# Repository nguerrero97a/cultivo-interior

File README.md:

# cultivo-interior

Dispositivo de control y monitoreo de un cultivo en un modulo de interior.

Diseñado por Nicolás Guerrero Arévalo.

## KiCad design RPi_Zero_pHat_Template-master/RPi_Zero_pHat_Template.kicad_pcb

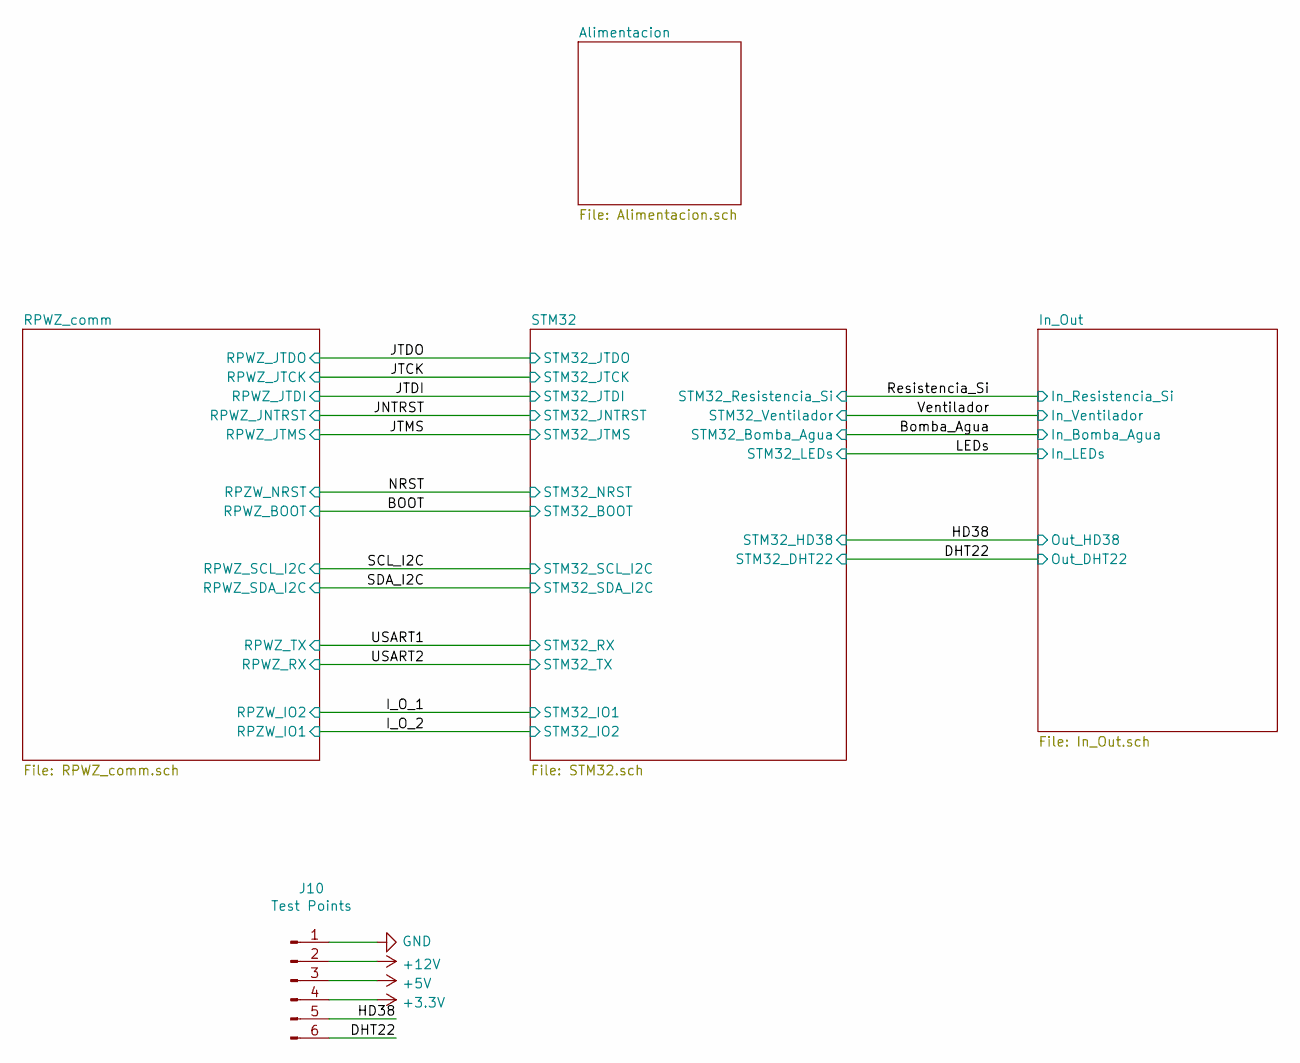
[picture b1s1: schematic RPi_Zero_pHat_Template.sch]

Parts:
J10: Test Points; PinHeader_1x06_P2.54mm_Vertical

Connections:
+3V3: J10.4; also elsewhere on the board
+5V: J10.3; also elsewhere on the board
+12V: J10.2; also elsewhere on the board
/DHT22: J10.6; also elsewhere on the board
/HD38: J10.5; also elsewhere on the board
GND: J10.1; also elsewhere on the board

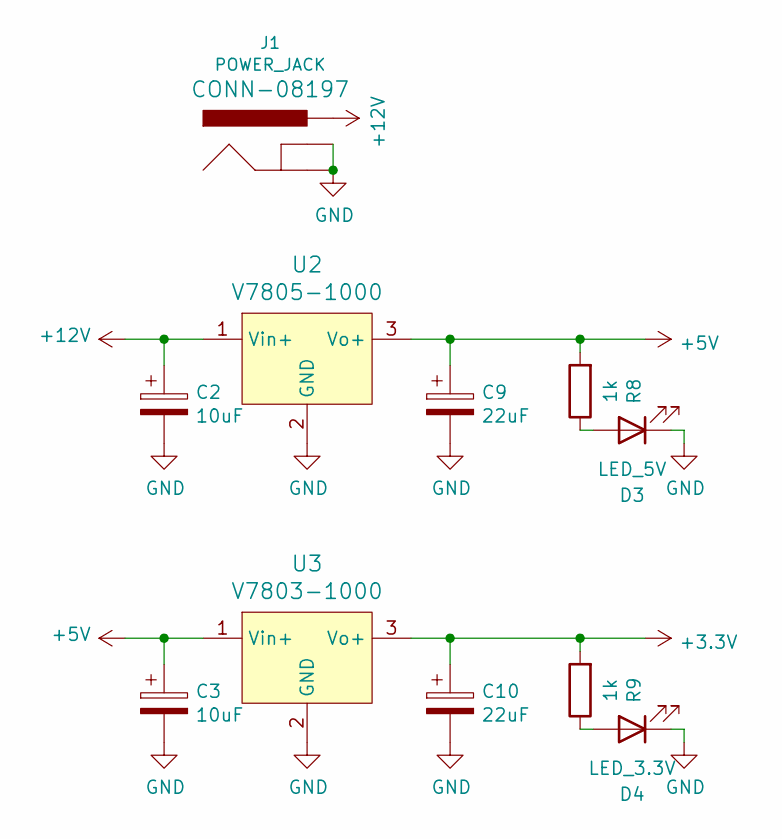
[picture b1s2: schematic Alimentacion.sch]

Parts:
C2, C3: 10uF; CP_Elec_4x5.8
C9, C10: 22uF; CP_Elec_3x5.4
D3: LED_5V; LED_0805_2012Metric
D4: LED_3.3V; LED_0805_2012Metric
J1: POWER_JACK; POWER_JACK_PTH
R8, R9: 1k; R_0805_2012Metric
U2: V7805-1000; 3-SIP_Module_V7805-1000; MPN V7805-1000; Digi-Key_PN 102-1715-ND
U3: V7803-1000; 3-SIP_Module_V7805-1000; MPN V7805-1000; Digi-Key_PN 102-1715-ND

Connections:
+3V3: C10.1, R9.2, U3.3 (Vo+); also elsewhere on the board
+5V: C3.1, C9.1, R8.2, U2.3 (Vo+), U3.1 (Vin+); also elsewhere on the board
+12V: C2.1, J1.PWR, U2.1 (Vin+); also elsewhere on the board
GND: C2.2, C3.2, C9.2, C10.2, D3.1 (K), D4.1 (K), J1.GND, J1.GNDB (GNDBREAK), U2.2 (GND), U3.2 (GND); also elsewhere on the board
unnamed: D3.2 (A), R8.1
unnamed: D4.2 (A), R9.1

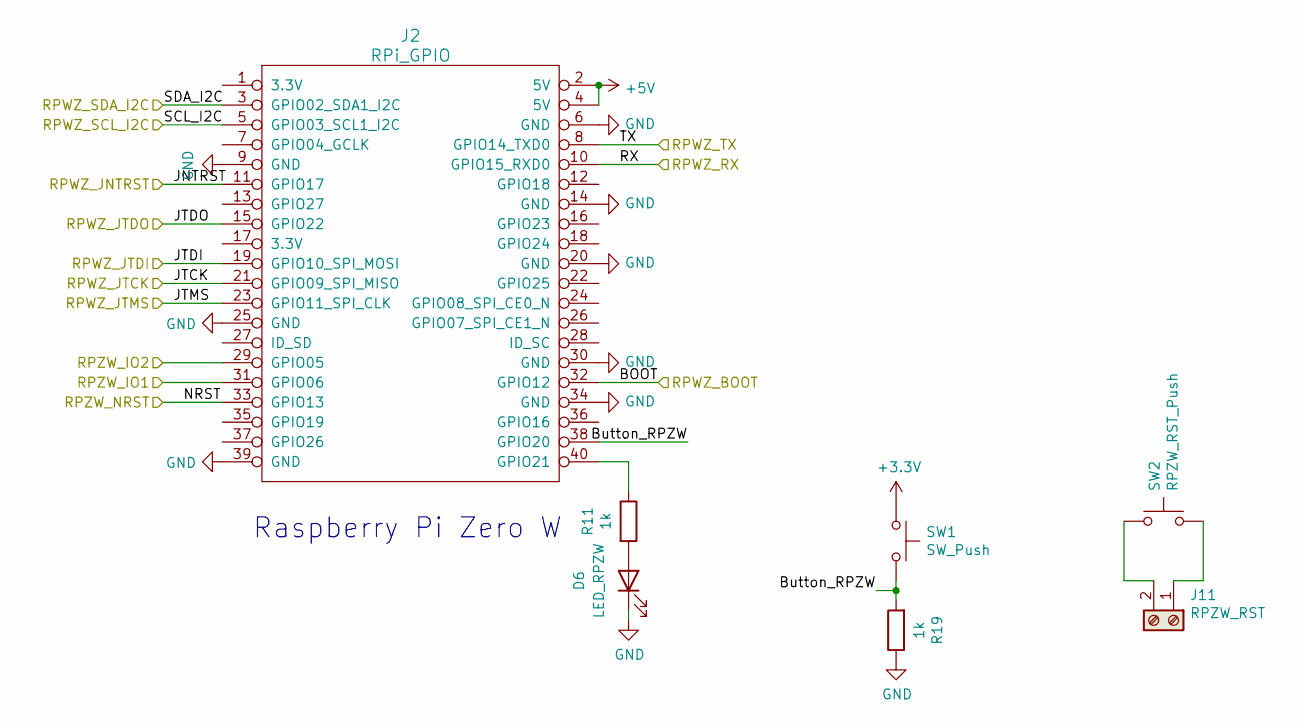
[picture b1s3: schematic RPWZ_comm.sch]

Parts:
D6: LED_RPZW; LED_0805_2012Metric
J2: RPi_GPIO; PinHeader_2x20_P2.54mm_Vertical
J11: RPZW_RST; PinHeader_1x02_P2.54mm_Vertical
R11, R19: 1k; R_0805_2012Metric
SW1: SW_Push; SW_PUSH_6mm_H4.3mm
SW2: RPZW_RST_Push; SW_PUSH_6mm_H4.3mm

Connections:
+3V3: SW1.1; also elsewhere on the board
+5V: J2.2 (5V), J2.4 (5V); also elsewhere on the board
/BOOT: J2.32 (GPIO12); also elsewhere on the board
/I_O_1: J2.29 (GPIO05); also elsewhere on the board
/I_O_2: J2.31 (GPIO06); also elsewhere on the board
/JNTRST: J2.11 (GPIO17); also elsewhere on the board
/JTCK: J2.21 (GPIO09_SPI_MISO); also elsewhere on the board
/JTDI: J2.19 (GPIO10_SPI_MOSI); also elsewhere on the board
/JTDO: J2.15 (GPIO22); also elsewhere on the board
/JTMS: J2.23 (GPIO11_SPI_CLK); also elsewhere on the board
/NRST: J2.33 (GPIO13); also elsewhere on the board
/RPWZ_comm/Button_RPZW: J2.38 (GPIO20), R19.2, SW1.2
/SCL_I2C: J2.5 (GPIO03_SCL1_I2C); also elsewhere on the board
/SDA_I2C: J2.3 (GPIO02_SDA1_I2C); also elsewhere on the board
/USART1: J2.8 (GPIO14_TXD0); also elsewhere on the board
/USART2: J2.10 (GPIO15_RXD0); also elsewhere on the board
GND: D6.1 (K), J2.6 (GND), J2.9 (GND), J2.14 (GND), J2.20 (GND), J2.25 (GND), J2.30 (GND), J2.34 (GND), J2.39 (GND), R19.1; also elsewhere on the board
unnamed: D6.2 (A), R11.2
unnamed: J2.40 (GPIO21), R11.1
unnamed: J11.1, SW2.2
unnamed: J11.2, SW2.1

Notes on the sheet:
Raspberry Pi Zero W

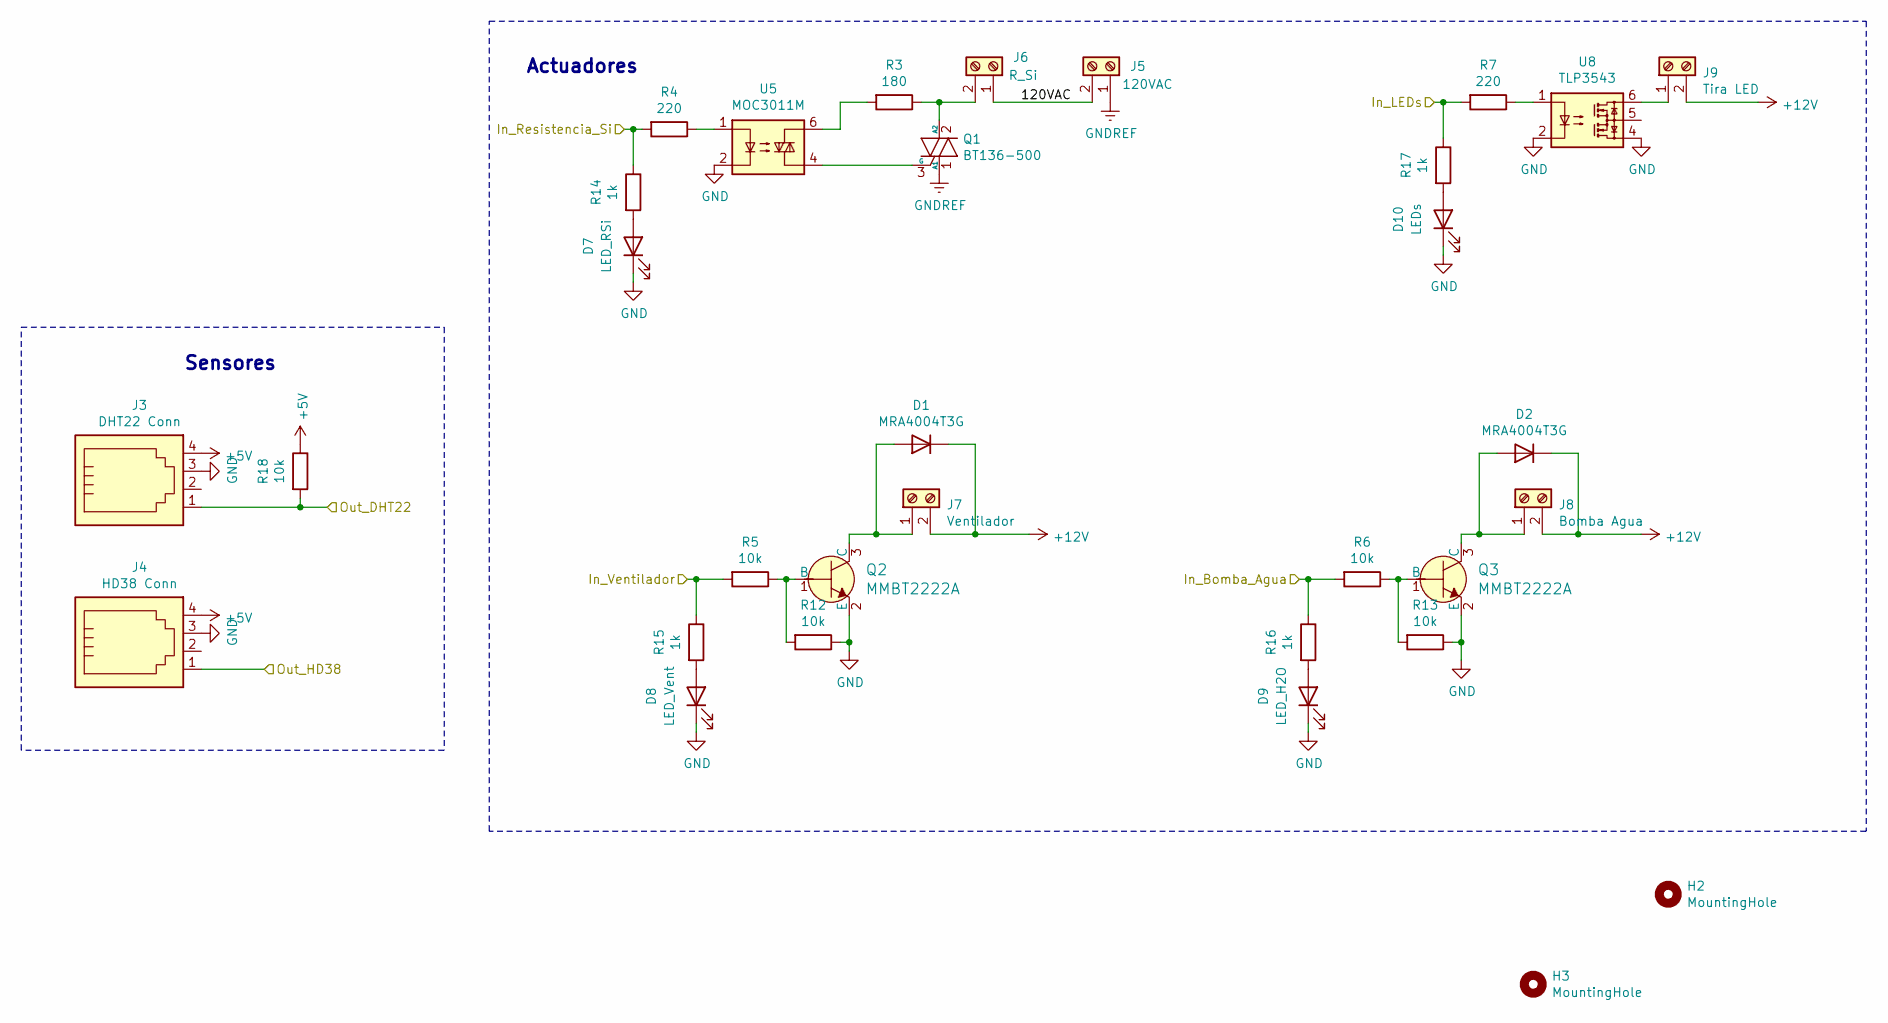
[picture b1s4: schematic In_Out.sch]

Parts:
D1, D2: MRA4004T3G; D_SMA
D7: LED_RSi; LED_0805_2012Metric
D8: LED_Vent; LED_0805_2012Metric
D9: LED_H2O; LED_0805_2012Metric
D10: LEDs; LED_0805_2012Metric
H2, H3: MountingHole; MountingHole_3.5mm
J3: DHT22 Conn; RJ9-4P4C
J4: HD38 Conn; RJ9-4P4C
J5: 120VAC; TerminalBlock_Phoenix_MKDS-1,5-2-5.08_1x02_P5.08mm_Horizont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
J6: R_Si; TerminalBlock_Phoenix_MKDS-1,5-2-5.08_1x02_P5.08mm_Horizont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
J7: Ventilador; TerminalBlock_Phoenix_MKDS-1,5-2-5.08_1x02_P5.08mm_Horizont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
J8: Bomba Agua; TerminalBlock_Phoenix_MKDS-1,5-2-5.08_1x02_P5.08mm_Horizont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
J9: Tira LED; TerminalBlock_Phoenix_MKDS-1,5-2-5.08_1x02_P5.08mm_Horizont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
Q1: BT136-500; TO-252-2
Q2, Q3: MMBT2222A; SOT-23-3; MPN MMBT2222A; Digi-Key_PN MMBT2222AFSCT-ND
R3: 180; R_1206_3216Metric
R4, R7: 220; R_0805_2012Metric
R5, R6, R12, R13, R18: 10k; R_0805_2012Metric
R14, R15, R16, R17: 1k; R_0805_2012Metric
U5: MOC3011M; OPTOCOUPLER_H11F3SR2M
U8: TLP3543; SOP254P700X210-6N

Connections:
+5V: J3.4, J4.4, R18.1; also elsewhere on the board
+12V: D1.1 (K), D2.1 (K), J7.2, J8.2, J9.2; also elsewhere on the board
/Bomba_Agua: R6.2, R16.1; also elsewhere on the board
/DHT22: J3.1, R18.2; also elsewhere on the board
/HD38: J4.1; also elsewhere on the board
/In_Out/120VAC: J5.2, J6.1
/LEDs: R7.2, R17.1; also elsewhere on the board
/Resistencia_Si: R4.2, R14.1; also elsewhere on the board
/Ventilador: R5.2, R15.1; also elsewhere on the board
GND: D7.1 (K), D8.1 (K), D9.1 (K), D10.1 (K), J3.3, J4.3, Q2.2 (E), Q3.2 (E), R12.1, R13.1, U5.2, U8.2, U8.4; also elsewhere on the board
GNDREF: J5.1, Q1.1 (A1)
unnamed: D1.2 (A), J7.1, Q2.3 (C)
unnamed: D2.2 (A), J8.1, Q3.3 (C)
unnamed: D7.2 (A), R14.2
unnamed: D8.2 (A), R15.2
unnamed: D9.2 (A), R16.2
unnamed: D10.2 (A), R17.2
unnamed: J6.2, Q1.2 (A2), R3.1
unnamed: J9.1, U8.6
unnamed: Q1.3 (G), U5.4
unnamed: Q2.1 (B), R5.1, R12.2
unnamed: Q3.1 (B), R6.1, R13.2
unnamed: R3.2, U5.6
unnamed: R4.1, U5.1
unnamed: R7.1, U8.1

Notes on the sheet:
Sensores
Actuadores

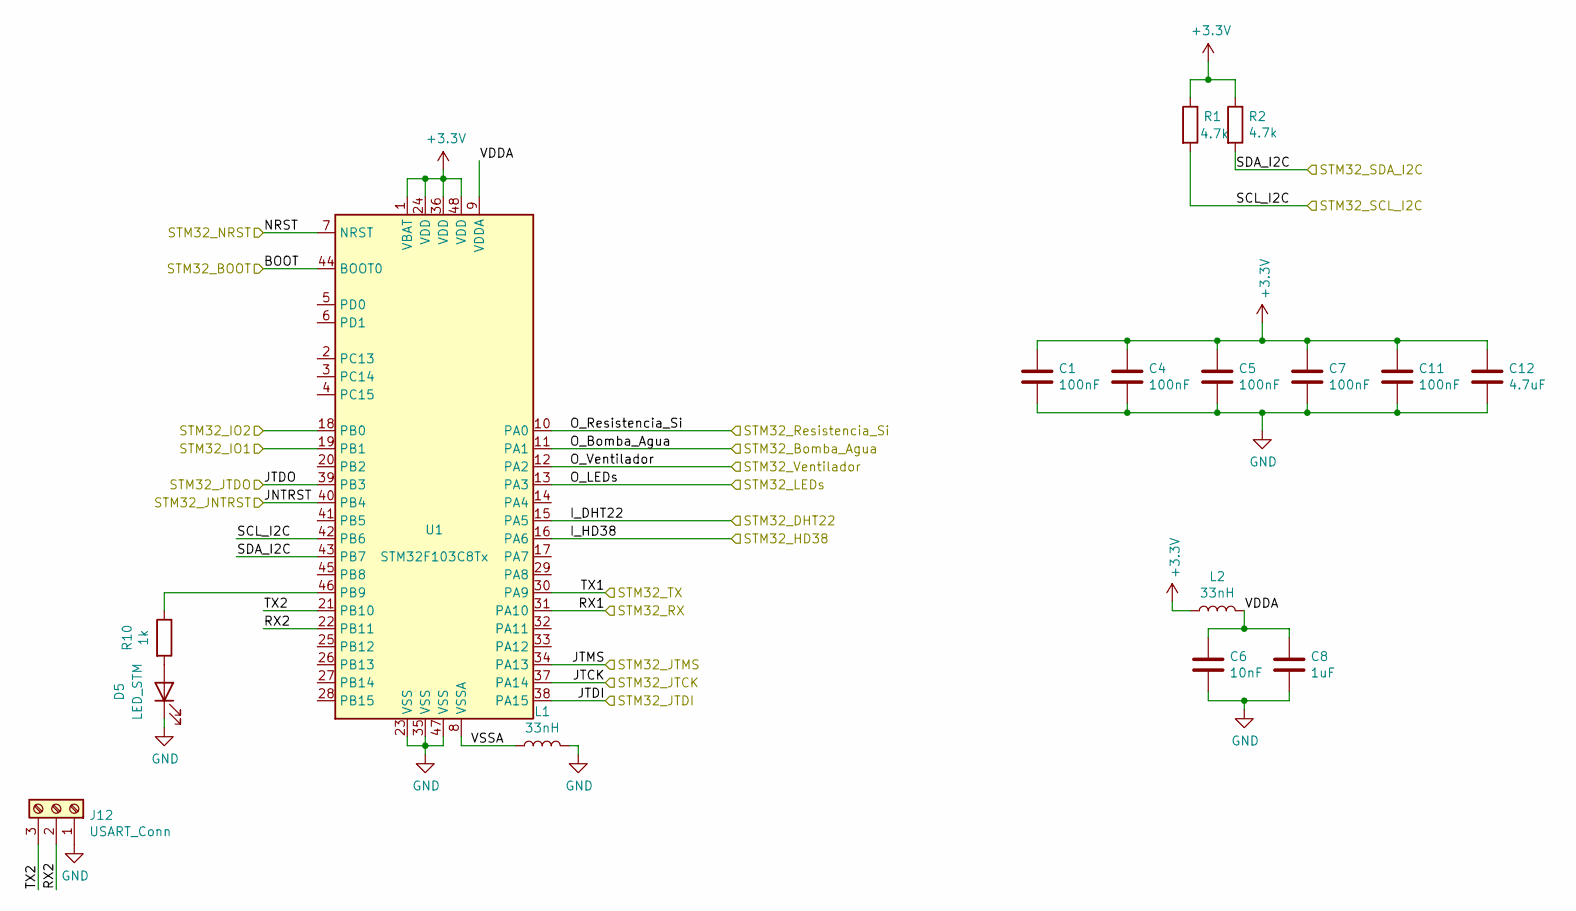
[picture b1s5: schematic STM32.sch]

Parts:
C1, C4, C5, C7, C11: 100nF; C_0805_2012Metric
C6: 10nF; C_0805_2012Metric
C8: 1uF; C_0805_2012Metric
C12: 4.7uF; C_0805_2012Metric
D5: LED_STM; LED_0805_2012Metric
J12: USART_Conn; PinHeader_1x03_P2.54mm_Vertical
L1, L2: 33nH; L_0603_1608Metric
R1, R2: 4.7k; R_0805_2012Metric
R10: 1k; R_0805_2012Metric
U1: STM32F103C8Tx; LQFP-48_7x7mm_P0.5mm

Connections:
+3V3: C1.1, C4.1, C5.1, C7.1, C11.1, C12.1, L2.1, R1.1, R2.1, U1.1 (VBAT), U1.24 (VDD), U1.36 (VDD), U1.48 (VDD); also elsewhere on the board
/BOOT: U1.44 (BOOT0); also elsewhere on the board
/Bomba_Agua: U1.11 (PA1); also elsewhere on the board
/DHT22: U1.15 (PA5); also elsewhere on the board
/HD38: U1.16 (PA6); also elsewhere on the board
/I_O_1: U1.19 (PB1); also elsewhere on the board
/I_O_2: U1.18 (PB0); also elsewhere on the board
/JNTRST: U1.40 (PB4); also elsewhere on the board
/JTCK: U1.37 (PA14); also elsewhere on the board
/JTDI: U1.38 (PA15); also elsewhere on the board
/JTDO: U1.39 (PB3); also elsewhere on the board
/JTMS: U1.34 (PA13); also elsewhere on the board
/LEDs: U1.13 (PA3); also elsewhere on the board
/NRST: U1.7 (NRST); also elsewhere on the board
/Resistencia_Si: U1.10 (PA0); also elsewhere on the board
/SCL_I2C: R1.2, U1.42 (PB6); also elsewhere on the board
/SDA_I2C: R2.2, U1.43 (PB7); also elsewhere on the board
/STM32/RX2: J12.2, U1.22 (PB11)
/STM32/TX2: J12.3, U1.21 (PB10)
/STM32/VDDA: C6.1, C8.1, L2.2, U1.9 (VDDA)
/STM32/VSSA: L1.1, U1.8 (VSSA)
/USART1: U1.31 (PA10); also elsewhere on the board
/USART2: U1.30 (PA9); also elsewhere on the board
/Ventilador: U1.12 (PA2); also elsewhere on the board
GND: C1.2, C4.2, C5.2, C6.2, C7.2, C8.2, C11.2, C12.2, D5.1 (K), J12.1, L1.2, U1.23 (VSS), U1.35 (VSS), U1.47 (VSS); also elsewhere on the board
unnamed: D5.2 (A), R10.2
unnamed: R10.1, U1.46 (PB9)

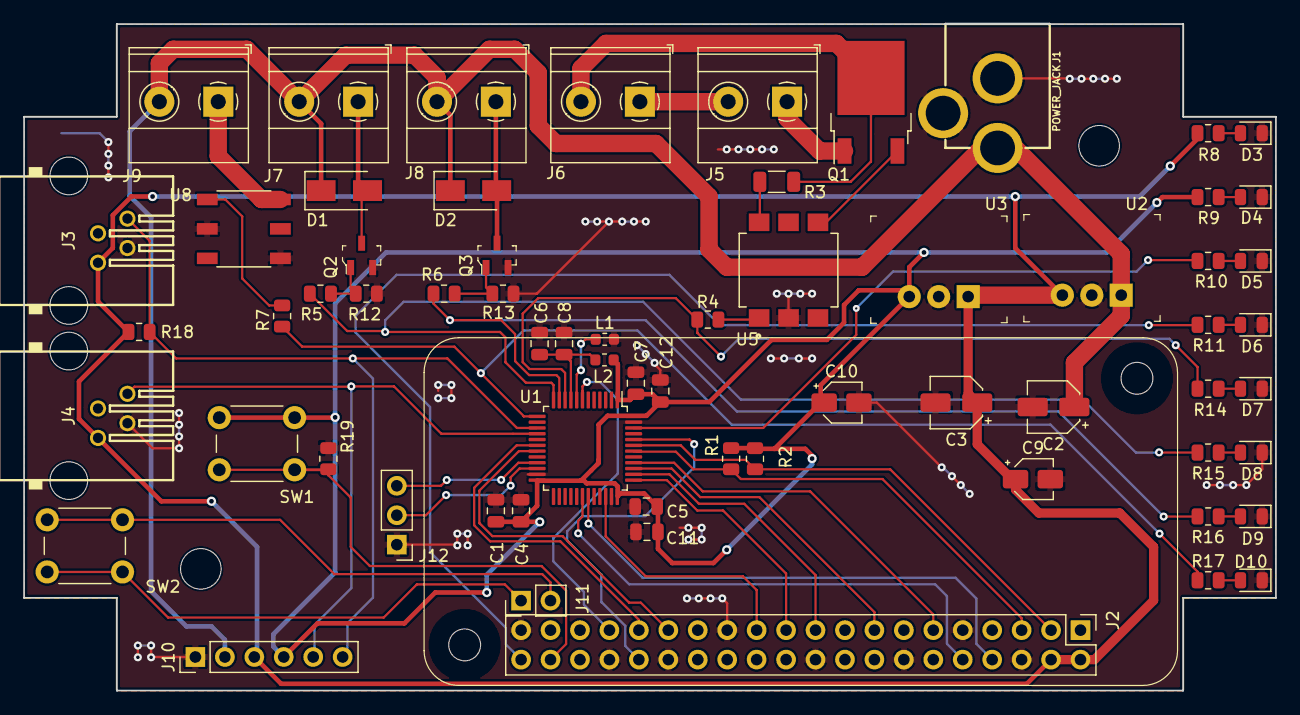
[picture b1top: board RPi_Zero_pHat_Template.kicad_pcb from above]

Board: 2 copper layers, 108.0 x 57.5 mm, 67 parts (0 on the bottom side), 52 nets.

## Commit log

2021-04-12 Archivos KiCad
2021-04-13 PDF Esquematico
2021-04-15 Diagrama de bloques
2021-04-15 Esquematico
